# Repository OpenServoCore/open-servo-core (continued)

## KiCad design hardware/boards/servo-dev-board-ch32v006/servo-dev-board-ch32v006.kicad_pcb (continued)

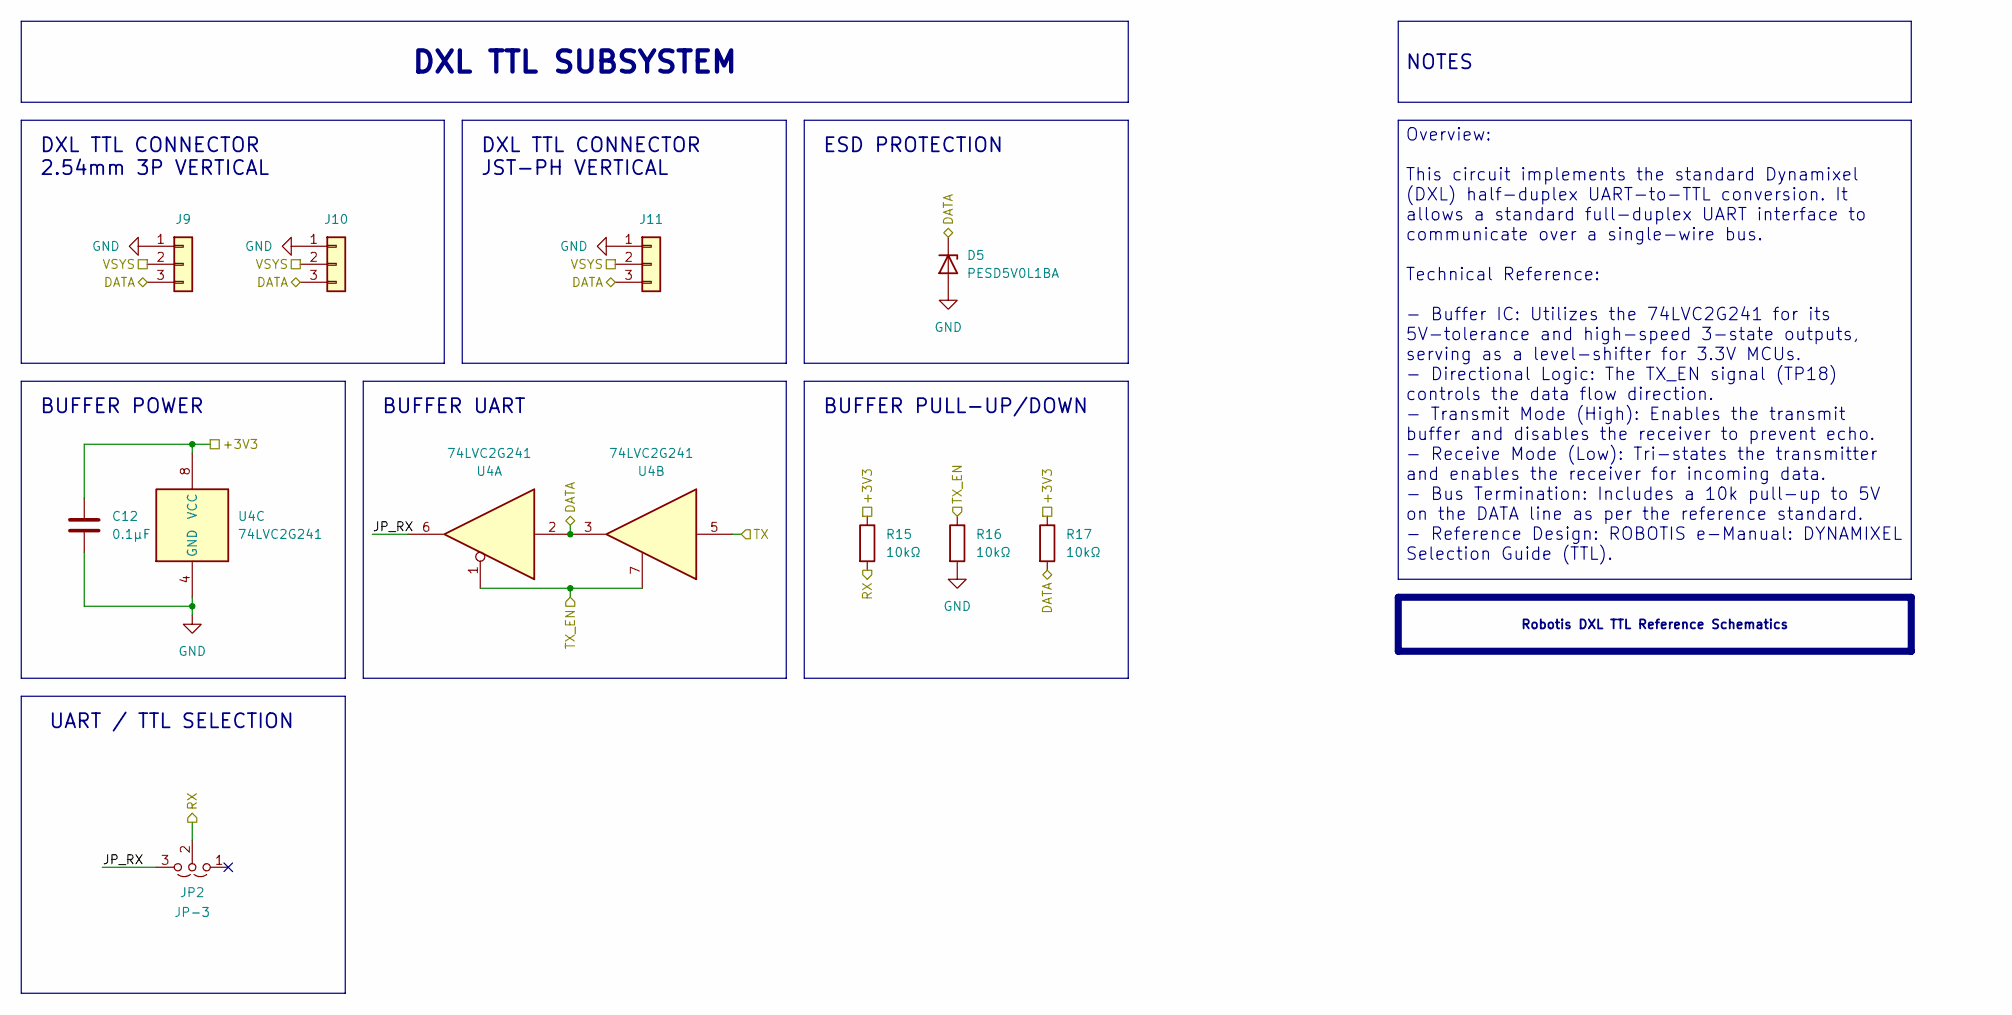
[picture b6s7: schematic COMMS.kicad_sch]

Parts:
C12: 0.1µF; C_0805_2012Metric_Pad1.18x1.45mm_HandSolder; LCSC C28233
D5: PESD5V0L1BA; D_SOD-323_HandSoldering; LCSC C2687118
J9, J10: PIN-1-3P; PinHeader_1x03_P2.54mm_Vertical; LCSC C49257
J11: JST-PH-V; CONN-TH_B3B-PH-K-S; JLC Type Extended
JP2: JP-3; PinHeader_1x03_P2.54mm_Vertical; LCSC C41425293
R15, R16, R17: 10kΩ; R_0805_2012Metric_Pad1.20x1.40mm_HandSolder; LCSC C17414
U4: 74LVC2G241; VSSOP-8_L2.3-W2.0-P0.50-LS3.1-BR; LCSC C10430

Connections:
+3V3: C12.1, R15.1, R17.1, U4.8 (VCC); also elsewhere on the board
/COMMS/JP_RX: JP2.3 (B), U4.6
/DATA: D5.1 (K), J9.3, J10.3, J11.3, R17.2, U4.2, U4.3; also elsewhere on the board
/RX: JP2.2 (C), R15.2; also elsewhere on the board
/TX: U4.5; also elsewhere on the board
/TX_EN: R16.1, U4.1, U4.7; also elsewhere on the board
GND: C12.2, D5.2 (A), J9.1, J10.1, J11.1, R16.2, U4.4 (GND); also elsewhere on the board
VSYS: J9.2, J10.2, J11.2; also elsewhere on the board

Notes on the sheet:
ESD PROTECTION
BUFFER UART
BUFFER PULL-UP/DOWN
DXL TTL CONNECTOR JST-PH VERTICAL
BUFFER POWER
UART / TTL SELECTION
DXL TTL CONNECTOR 2.54mm 3P VERTICAL
Overview: This circuit implements the standard Dynamixel (DXL) half-duplex UART-to-TTL conversion. It allows a standard full-duplex UART interface to communicate over a single-wire bus. Technical Reference: - Buffer IC: Utilizes the 74LVC2G241 for its 5V-tolerance and high-speed 3-state outputs, se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
DXL TTL SUBSYSTEM
Robotis DXL TTL Reference Schematics
NOTES

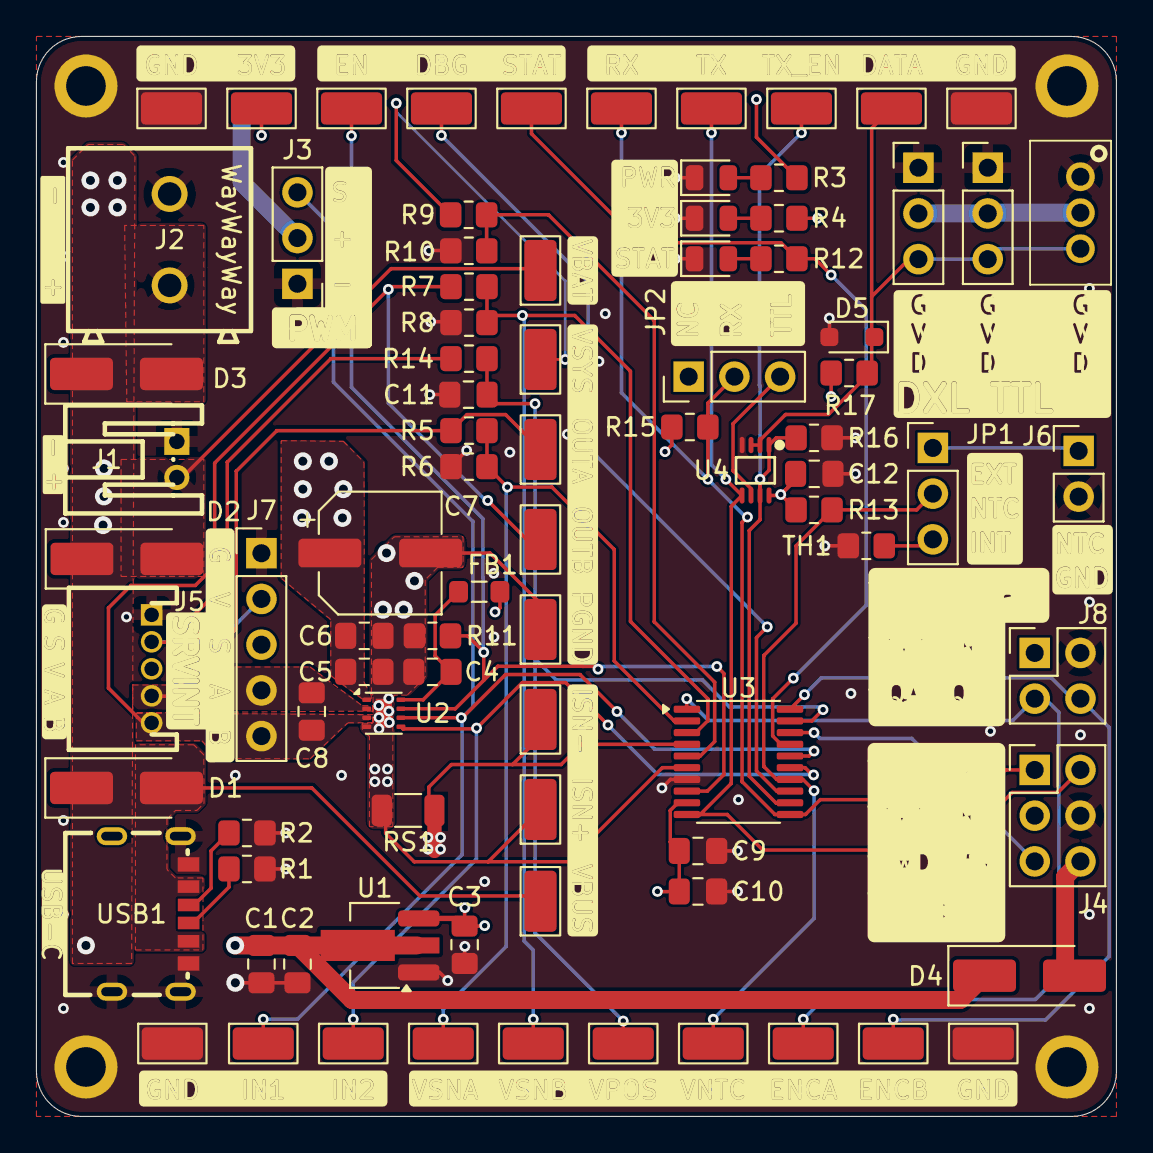
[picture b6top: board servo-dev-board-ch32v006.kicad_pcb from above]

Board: 4 copper layers, 60.0 x 60.0 mm, 92 parts (0 on the bottom side), 39 nets.

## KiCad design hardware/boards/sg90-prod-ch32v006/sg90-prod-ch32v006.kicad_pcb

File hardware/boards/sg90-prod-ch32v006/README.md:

# OSC SG90 CH32

> ⚠️ **Designed, not spun. Pre-fabrication, pre-bringup.**
> This board has never been fabbed. Numbers and behaviour described below are **design intent**, not measured. The schematic and layout exist; the firmware they're meant to run does not yet — firmware v2 is unstarted as of this writing. Don't fab this without doing your own review first, and expect changes when bringup finally happens.

OpenServoCore swap board for SG90-class hobby servos. Compact, double-sided, designed to physically replace the factory PCB inside an SG90 case. CH32V006-based, DXL-compatible half-duplex UART, drop-in mechanical fit.

## Overview

- **MCU** — CH32V006F8U6 (RISC-V, 48 MHz, 62 KB flash, 8 KB RAM).
- **Motor driver** — TI DRV8837 H-bridge (1.8 A peak, IN1/IN2 PWM).
- **LDO** — TPAP2210K-3.3, 3.3 V logic rail.
- **UART buffer** — SN74LVC1G07 open-drain for half-duplex DXL.
- **Current shunt** — 25 mΩ, 1 % on the low side.
- **Power input** — 3.3-8.4 V (1S-2S LiPo) via the servo cable.
- **Debug** — 4-pad SWD interface for WCH-LinkE.
- **Position feedback** — existing servo potentiometer wiper.
- **Form factor** — 10 × 12.5 mm, double-sided assembly.

## Connectors

### Servo cable — J1 (1×3, through-hole pads)

Standard hobby-servo 3-wire pinout, but the signal pin carries half-duplex UART instead of PWM:

| Pin | Net    | Notes                                   |
| --- | ------ | --------------------------------------- |
| 1   | `VIN`  | 3.3-8.4 V (1S-2S LiPo).                 |
| 2   | `DATA` | Half-duplex UART, baud TBD by firmware. |
| 3   | `GND`  |                                         |

### Motor — J2 (2 wire pads)

Solder directly to the SG90 motor leads.

| Pad    | Net              |
| ------ | ---------------- |
| `OUTA` | Motor terminal A |
| `OUTB` | Motor terminal B |

### Potentiometer — J3 (3 pads)

Connects to the existing servo potentiometer.

| Pad    | Net          |
| ------ | ------------ |
| `+3V3` | Pot top rail |
| `VPOS` | Wiper        |
| `GND`  | Pot ground   |

### Debug — J4 (4 pads, 1.27 mm pitch)

Single-wire SWD for WCH-LinkE. Programmed via `wlink` / `probe-rs`. Firmware build instructions land when firmware v2 starts; until then there's nothing to flash.

| Pad | Net     |
| --- | ------- |
| 1   | `+3V3`  |
| 2   | `GND`   |
| 3   | `SWDIO` |
| 4   | `NC`    |

## Design intent

These are the targets the board was laid out around. None are measured.

- **Power architecture** — VIN routes to the DRV8837 directly; 3.3 V logic rail off the TPAP2210K LDO. Bulk capacitance is 2× 10 µF on VIN. PGND/GND joined at a single net tie.
- **Position sensing** — 12-bit ADC on `VPOS` with an RC filter (10 kΩ + 100 nF, fc ≈ 160 Hz) to suppress wiper noise. Sub-degree resolution is the design goal; actual precision waits on bringup and firmware oversampling.
- **Voltage sensing** — 20 kΩ / 10 kΩ dividers (ratio 0.333) on `VINS`, `VSNA`, `VSNB`. 8.4 V → 2.8 V at the ADC.
- **Current sensing** — 25 mΩ low-side shunt, sized for the DRV8837's ~1.76 A peak via `R_shunt ≈ 44 mV / I_stall`, so the hardware stall-detect path trips near the driver's max output. Raw V_shunt = 25 mV at 1 A; firmware sets ADC sampling, gain path, and software overcurrent threshold.
- **Communication** — DXL-style half-duplex UART. The SN74LVC1G07 open-drain buffer enables bidirectional comms over the single `DATA` line. Baud rate TBD — left to firmware v2 to choose.
- **Protection** — PESD5V0L1UL TVS on `DATA`.

## Assembly

Double-sided assembly, no vias-in-pads. Suitable for hot-plate / hot-air / IR reflow, or JLCPCB SMT. The board is 8-layer for routing density at this size.

## Mechanical fit

Designed to drop into a standard SG90 servo case:

- Motor leads solder to `OUTA` / `OUTB`.
- Pot wiper connects to `J3`.
- Servo cable connects to `J1`.
- Debug pads remain accessible through the case opening for bringup / reflashing.

Pad spacing for motor leads and debug pitch are still **to be confirmed against a physical case** when first boards arrive.

## License

Hardware files (schematic, layout, board files in this directory) are licensed under [CERN-OHL-P v2.0](../../../LICENSE-HARDWARE). See the [top-level README](../../../README.md#license) for the full licensing picture.

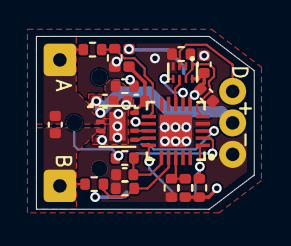
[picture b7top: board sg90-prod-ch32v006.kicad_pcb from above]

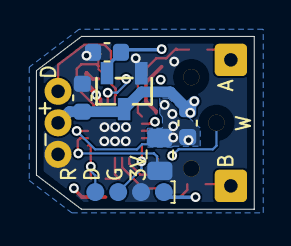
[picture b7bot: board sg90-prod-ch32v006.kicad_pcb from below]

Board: 4 copper layers, 12.1 x 9.6 mm, 31 parts (8 on the bottom side), 23 nets.

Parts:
C1, C2, C10: 10µF; C_0603_1608Metric
C4, C6, C7, C8, C9, C11: 0.1µF; C_0402_1005Metric
FB1: 600Ω@100MHz; L_0402_1005Metric
J1: Servo Input; Servo_Output_Pads
J2: Motor; Motor_Wire_Pads
J3: Debug; Debug_Pads_1x4_P1.27mm
J4: Potentiometer; Pot_Wire_Pads
NT1, NT2: NetTie_2; NetTie-2_SMD_0.127mm
R1, R3, R4, R6, R8, R9: 10kΩ; R_0402_1005Metric
R2: 4.7kΩ; R_0402_1005Metric
R5, R7: 20kΩ; R_0402_1005Metric
RS1: 10mΩ 1%; R_0805_2012Metric
TH1: NTC 10k; R_0402_1005Metric
U1: H7133-1_C277537; SOT-23-3_L2.9-W1.3-P1.90-LS2.4-BR
U4: DRV8837; WSON-8-1EP_2x2mm_P0.5mm_EP0.9x1.6mm
U5: CH32V006F8U6; UQFN-20_L3.0-W3.0-P0.40-BL-EP1.7
U6: 74LVC2G241GS,115; XSON-8_L1.4-W1.0-P0.35-S0.55-BL

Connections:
+3V3: C2.1, C4.1, C11.1, FB1.1, J3.1, J4.3, R4.1, R9.1, U1.2 (VOUT), U5.6 (VDD), U6.8 (VCC)
/3V3_DRV: C7.1, FB1.2, U4.8 (VCC)
/DATA: J1.3, U6.2 (1A), U6.3 (2Y)
/EN: R3.1, U4.7 (~SLEEP), U5.12 (PC5/T1C2_7)
/IN1: U4.6 (IN1), U5.13 (PC6/T1C1_2)
/IN2: U4.5 (IN2), U5.14 (PC7/T1C3_3)
/ISNS+: NT1.1, U5.3 (PA2/OPP0)
/ISNS-: NT2.1, U5.2 (PA1/OPN0)
/MOT_A: C8.1, J2.1, R5.1, U4.2 (OUT1)
/MOT_B: C8.2, J2.2, R7.1, U4.3 (OUT2)
/POT: J4.2, R2.1
/RX: U5.8 (PC1/RX_3), U6.6 (1Y)
/SWDIO: J3.3, U5.15 (PD1/SWIO)
/TX: U5.7 (PC0/TX_3/T1C3_2), U6.5 (2A)
/TX_EN: R1.2, U5.5 (PD0/TX_2), U6.1 (~1OE), U6.7 (2OE)
/VNTC: R9.2, TH1.1, U5.18 (PD4/A7)
/VPOS: C6.1, R2.2, U5.16 (PD2/A3)
/VSNA: R5.2, R6.1, U5.11 (PC4/A2)
/VSNB: R7.2, R8.1, U5.17 (PD3/A4)
/nRST: J3.4, R4.2, U5.1 (PD7/RST)
GND: C1.2, C2.2, C4.2, C6.2, C11.2, J1.1, J3.2, J4.1, NT2.2, R1.1, R6.2, R8.2, RS1.1, TH1.2, U1.1 (GND), U5.4 (VSS), U5.21 (VSS), U6.4 (GND)
PGND: C7.2, C9.2, C10.2, NT1.2, R3.2, RS1.2, U4.4 (GND), U4.9 (GND)
VSYS: C1.1, C9.1, C10.1, J1.2, U1.3 (VIN), U4.1 (VM)

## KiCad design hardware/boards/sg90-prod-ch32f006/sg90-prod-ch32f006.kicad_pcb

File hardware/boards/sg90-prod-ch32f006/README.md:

# SG90 Servo Controller Board - CH32V006

A compact, high-precision servo controller designed to replace the control circuitry in SG90/MG90 servo clones. This single-sided board fits within a 10x12.5mm footprint while providing advanced features like back-EMF sensing, overcurrent protection, and 0.1-0.2° position precision.

## Features

- **MCU**: CH32V006F8U6 RISC-V microcontroller (48MHz, 32KB flash, 4KB RAM)
- **Motor Driver**: Integrated DRV8837C H-bridge (1.8A peak)
- **Position Sensing**: 12-bit ADC with RC filtering for 0.1-0.2° precision
- **Current Sensing**: 0.1Ω shunt with internal op-amp
- **Protection**: P-channel MOSFET reverse polarity protection (17mΩ RDS(on))
- **Communication**: 2Mbps half-duplex UART over single DATA line
- **Power**: 5V operation, no LDO required
- **Size**: 10x12.5mm, single-sided assembly
- **Debug**: 4-pin SWD interface for programming with WCH-LinkE

## Specifications

- Input Voltage: 4.5-5.5V
- Continuous Current: 200mA (typical servo operation)
- Peak Current: 1A (stall condition)
- Position Resolution: 0.044°/count (4096 counts over 180°)
- PWM Frequency: 10kHz center-aligned
- Communication: 2Mbps half-duplex UART
- Temperature Range: -40°C to +85°C

## Bill of Materials (BOM)

| Ref | Description | Package | LCSC # | Qty | Unit Price @5 | Unit Price @150 | Unit Price @500 |
|-----|-------------|---------|--------|-----|---------------|-----------------|-----------------|
| U1 | CH32V006F8U6 MCU | QFN-20 3x3mm | C42431288 | 1 | $0.2643 | $0.1838 | $0.1537 |
| U2 | DRV8837CDSGR Motor Driver | WSON-8 | C191000 | 1 | $0.098 | $0.0666 | $0.0587 |
| U3 | 74LVC1G07DSFR Buffer | TDFN-6 1x1mm | C42445855 | 1 | $0.0466 | $0.0317 | $0.0280 |
| Q1 | BRCS150P02ZJ P-MOSFET | DFN-6 2x2mm | C22448985 | 1 | $0.0747 | $0.0522 | $0.0466 |
| R1 | 10kΩ 1% | 0603 | Generic | 1 | $0.01 | $0.002 | $0.002 |
| R2 | 0.1Ω 1% 1/4W | 0603/0805 | Generic | 1 | $0.02 | $0.003 | $0.003 |
| R3 | 10kΩ 1% | 0603 | Generic | 1 | $0.01 | $0.002 | $0.002 |
| R4,R5 | 10kΩ 1% | 0603 | Generic | 2 | $0.01 | $0.002 | $0.002 |
| R6,R7 | 0Ω | 0603 | Generic | 2 | $0.01 | $0.001 | $0.001 |
| R8 | 0Ω | 0603 | Generic | 1 | $0.01 | $0.001 | $0.001 |
| R9 | 10kΩ 1% | 0603 | Generic | 1 | $0.01 | $0.002 | $0.002 |
| R10 | 1kΩ 1% | 0603 | Generic | 1 | $0.01 | $0.002 | $0.002 |
| C1,C2 | 100nF 16V X7R | 0603 | Generic | 2 | $0.01 | $0.002 | $0.002 |
| C3 | 1µF 16V X7R | 0603 | Generic | 1 | $0.01 | $0.003 | $0.003 |
| C4,C5 | 10µF 10V X5R | 0603/0805 | Generic | 2 | $0.02 | $0.005 | $0.004 |
| C6 | 100nF 16V X7R | 0603 | Generic | 1 | $0.01 | $0.002 | $0.002 |
| **Components Total** | | | | | **$0.664** | **~$0.35** | **$0.326** |
| **PCB** | 10x12.5mm 4-layer | - | - | 1 | **$1.40** | **$0.25** | **$0.11** |
| **TOTAL per board** | | | | | **$2.064** | **$0.60** | **$0.436** |
| **TOTAL** | | | | | **$10.32** | **$90.00** | **$218.00** |

### Cost Breakdown by Quantity

#### Prototype Run (5 boards)
- Components (5 sets): $0.664 × 5 = $3.32
- PCB (5 boards): $2.00 + $5.00 shipping = $7.00
- **Total for 5 boards: $10.32**
- **Cost per board: $2.06**
- **Selling at $3/board: $15 revenue - Profit: $4.68 (45% margin)**
- **Selling at $5/board: $25 revenue - Profit: $14.68 (142% margin)**

#### Small Production (150 boards)
- Components (150 sets): ~$0.35 × 150 = $52.50
- PCB (150 boards): $32.00 + $5.00 shipping = $37.00
- **Total for 150 boards: $89.50**
- **Cost per board: $0.60**
- **Selling at $2-3/board: $300-450 revenue**
- **Gross profit: $210.50-360.50**

#### Medium Production (500 boards)
- Components (500 sets): $0.326 × 500 = $163.00
- PCB (500 boards): $50.20 + $5.00 shipping = $55.20
- **Total for 500 boards: $218.20**
- **Cost per board: $0.44**
- **Selling at $2/board: $1,000 revenue**
- **Gross profit: $781.80 (358% markup!)**

*Prices shown are from LCSC in USD. Passive component prices are estimates for generic parts.*

## Pinout

### Power Connector (J1) - 3 pins
1. V_IN (5V)
2. DATA (Half-duplex UART, 2Mbps)
3. GND

### Motor Connector (J3) - 2 wire pads
1. MOT_A - Motor terminal A (7.4mm spacing)
2. MOT_B - Motor terminal B

### Potentiometer Connector (J2) - 3 pads
1. POT_VCC - Potentiometer power (5V)
2. POT_WIPER - Position feedback
3. POT_GND - Potentiometer ground

### Debug Interface (J4) - 4 pads, 1.27mm pitch
1. 5V - Power from debugger
2. GND - Ground
3. SWDIO - Single-wire debug
4. NC - Not connected

## Design Notes

### Power Architecture
- Single 5V rail operation eliminates need for LDO
- P-channel MOSFET provides reverse polarity protection with only 17mV drop at 1A
- Bulk capacitance (2x10µF) handles motor transients
- No ferrite bead needed due to synchronized ADC sampling

### ADC Precision
- 12-bit ADC provides 22.8 counts per degree (0.044°/count theoretical)
- RC filter (1kΩ + 100nF) on POT input reduces wiper noise
- 4-16x oversampling in firmware improves effective resolution
- Center-aligned PWM with mid-duty ADC sampling avoids switching noise

### Current Sensing
- 0.1Ω shunt resistor in series with motor ground
- Internal op-amp amplifies voltage drop
- ADC watchdog enables hardware overcurrent protection
- Kelvin connections (0Ω resistors R6,R7) for accurate sensing

### Communication
- Half-duplex UART at 2Mbps over single DATA line
- 74LVC1G07 open-drain buffer enables bidirectional communication
- 10kΩ pullup (R1) sized for 2Mbps operation
- Compatible with standard servo protocols

## Assembly

This board is designed for single-sided assembly, making it ideal for:
- Hot plate reflow
- Hot air station
- IR oven
- JLCPCB assembly service

All components are on the top side with no vias in pads.

## Programming

Program using WCH-LinkE debugger/programmer:
- Supports 5V target voltage
- Single-wire debug (SWD) interface
- Compatible with MounRiver Studio IDE
- printf debugging available over SWD

## Mechanical Integration

The board is designed to fit inside standard SG90 servo cases:
- Motor wires solder directly to MOT_A/MOT_B pads
- Potentiometer wires connect to J2
- Servo cable connects to J1
- Debug pads accessible through case opening

## Performance Targets

- Position accuracy: ±0.1-0.2°
- Position resolution: 0.044°
- Update rate: 10kHz
- Current limit: 1A (configurable via firmware)
- Continuous operation: 200mA
- Response time: <1ms
- Backdrive detection: Yes (via back-EMF)

## Manufacturing

Optimized for low-cost production:
- Total BOM cost: ~$0.43 at 500 qty
- Single-sided assembly reduces assembly cost
- Standard 0603 passives (except current shunt)
- All components available from LCSC
- 4-layer PCB for better thermal management

## TODO / Future Improvements

### Critical Values to Double-Check Before PCB Routing
- [ ] **Current shunt (R2):** Verify 0.1Ω gives good ADC range (0-330mV at 1A through 3.3x op-amp gain)
- [ ] **Voltage dividers (R4/R5):** Confirm 10kΩ divider properly scales 5V motor to ADC range
- [ ] **UART pullup (R1):** Verify 10kΩ optimal for 2Mbps half-duplex
- [ ] **RC filter (R10/C6):** Check 1kΩ + 100nF = 1.6kHz cutoff for POT noise
- [ ] **Bulk caps (C4/C5):** Confirm 2x10µF sufficient for motor transients
- [ ] **P-MOSFET RDS(on):** Verify 17mΩ = 17mV drop at 1A peak is acceptable
- [ ] **Motor pad spacing:** Confirm 7.4mm (3.7mm each side from center)
- [ ] **Debug pad pitch:** Verify 1.27mm for pogo pins
- [ ] **Package sizes:** Verify all footprints match actual parts (especially QFN-20)

### Rev B Changes
1. **Add test points on back side**
   - Add second 1x4 array at 1.27mm pitch (same as debug interface)
   - Uses same pogo pin clip for both programming and testing
   - **Debug array (1x4):** 5V, GND, SWDIO, NC (existing)
   - **Test array (1x4):** SEN_I, SEN_POT, PWM_A, V_MCU
   - Both arrays accessible from back when installed in servo
   - *Rationale: Single pogo clip tool works for both debug and test*

2. **Add ESD protection**
   - TVS diode on DATA line (SOD-523 or 0402 package)
   - Protects against ESD during cable plug/unplug
   - Suggested part: PESD5V0S1BL or similar 5.5V TVS (~$0.05)

3. **Consider fiducial marker**
   - Single 1mm fiducial for JLCPCB assembly alignment
   - Only if assembly house requires it

### Firmware Features (Planned)
- Backlash compensation
- Temperature compensation
- Position calibration LUT
- Multi-drop addressing
- Synchronized motion commands

## License

[Add your license here]

## Author

[Add author information here]

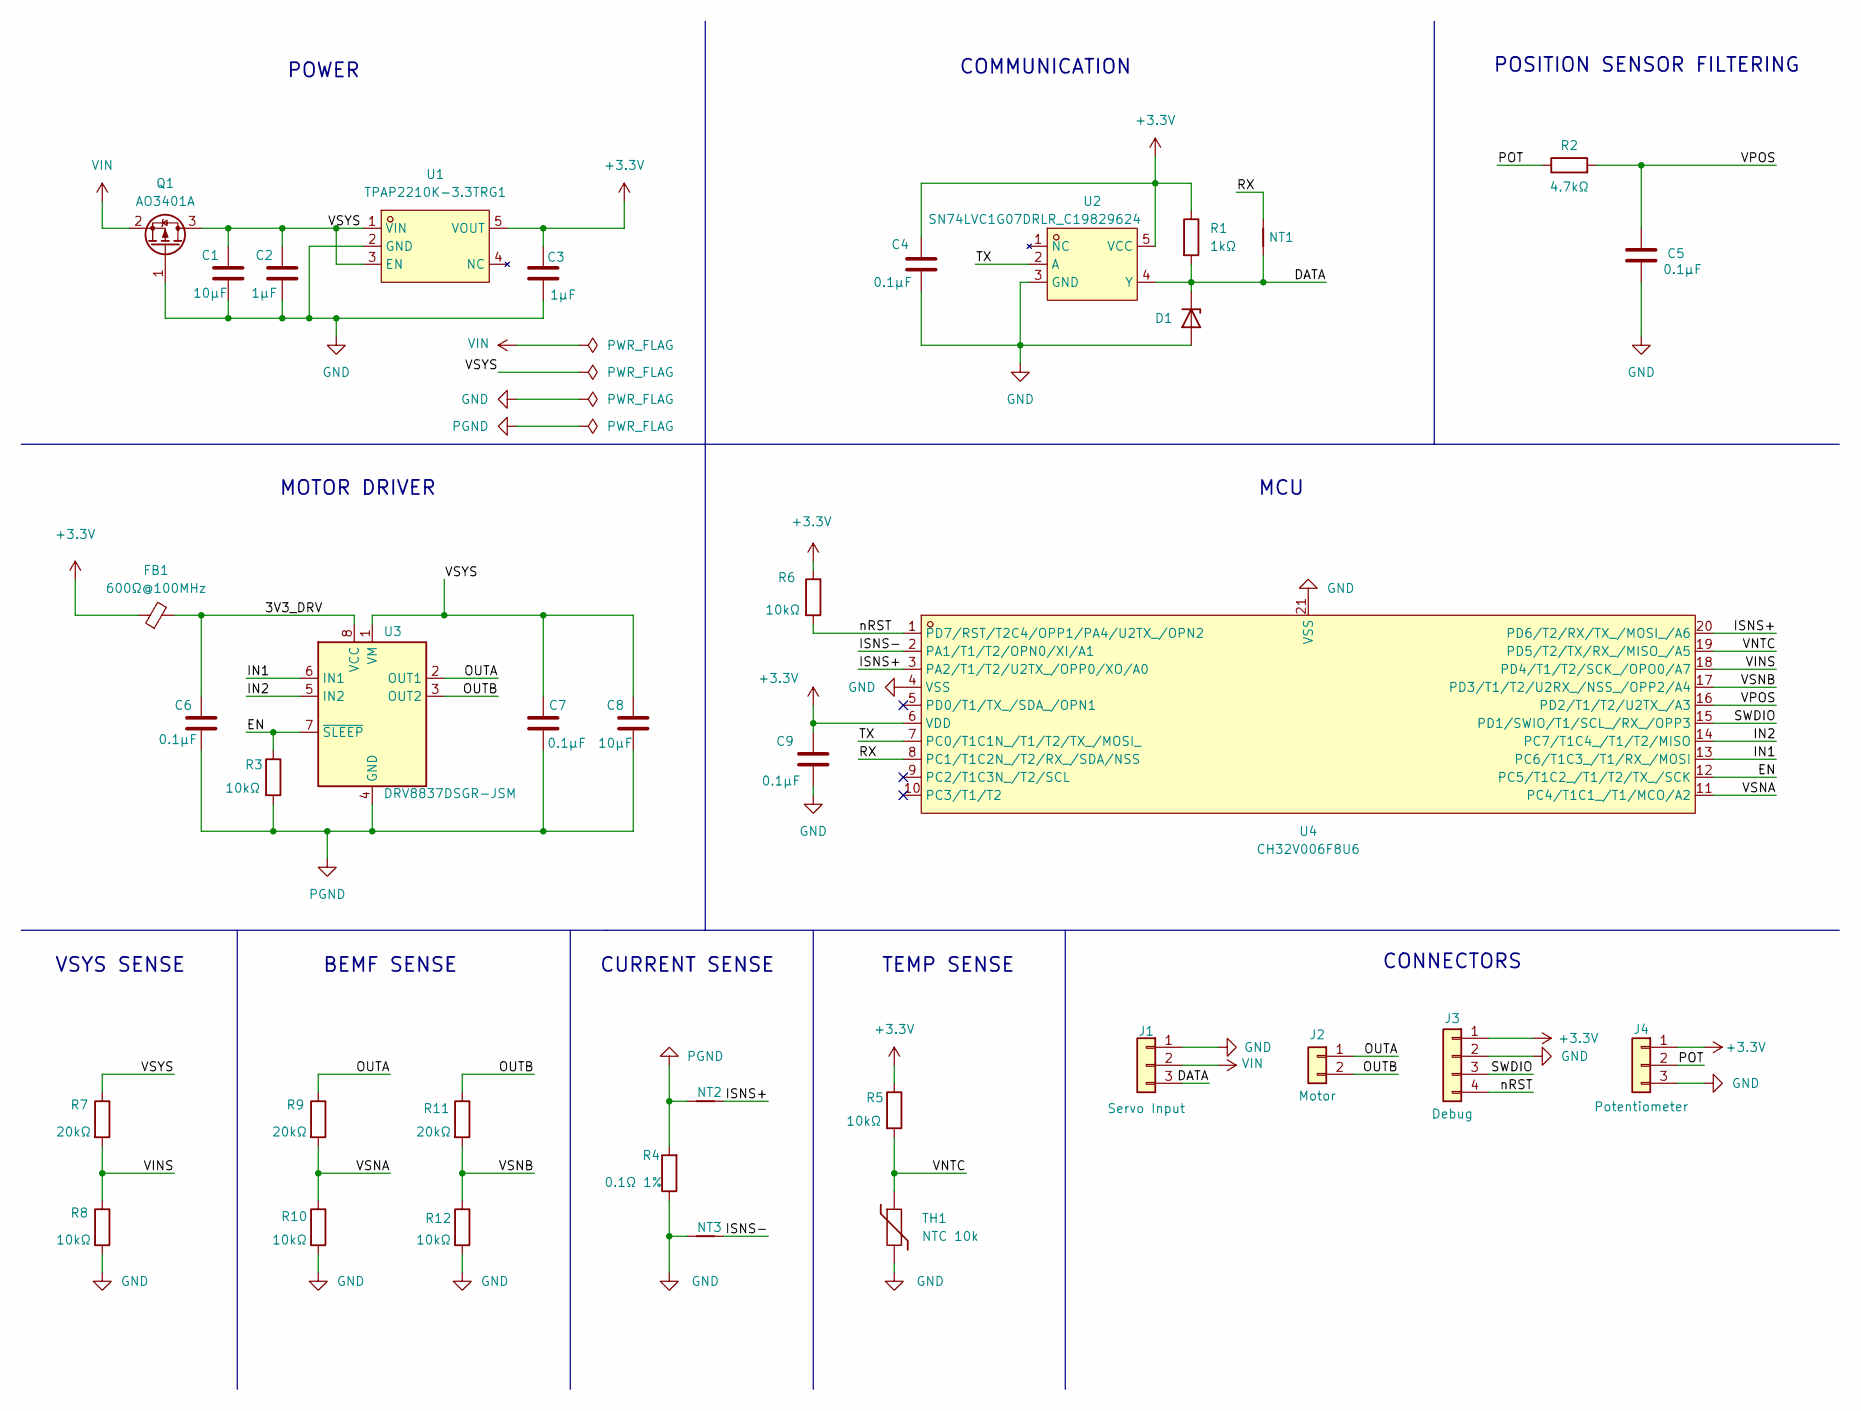
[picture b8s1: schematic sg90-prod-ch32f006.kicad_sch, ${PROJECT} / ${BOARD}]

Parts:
C1, C8: 10µF; C_0603_1608Metric
C2, C3: 1µF; C_0402_1005Metric
C4, C5, C6, C7, C9: 0.1µF; C_0402_1005Metric
D1: PESD5V0L1UL; D_SOD-882
FB1: 600Ω@100MHz; L_0603_1608Metric
J1: Servo Input; Servo_Output_Pads
J2: Motor; Motor_Wire_Pads
J3: Debug; Debug_Pads_1x4_P1.27mm
J4: Potentiometer; Pot_Wire_Pads
NT1, NT2, NT3: NetTie_2; NetTie-2_SMD_0.2mm
Q1: AO3401A; SOT-23
R1: 1kΩ; R_0402_1005Metric
R2: 4.7kΩ; R_0402_1005Metric
R3, R5, R6, R8, R10, R12: 10kΩ; R_0402_1005Metric
R4: 0.1Ω 1%; R_1206_3216Metric
R7, R9, R11: 20kΩ; R_0402_1005Metric
TH1: NTC 10k; R_0402_1005Metric
U1: TPAP2210K-3.3TRG1; SOT-23-5_L2.9-W1.6-P0.95-LS2.8-BR; LCSC Part C49190789
U2: SN74LVC1G07DRLR_C19829624; SOT-553-5_L1.6-W1.2-P0.50-LS1.6-BL; LCSC Part C19829624
U3: DRV8837DSGR-JSM; WSON-8-1EP_2x2mm_P0.5mm_EP0.9x1.6mm; LCSC C22447132
U4: CH32V006F8U6; UQFN-20_L3.0-W3.0-P0.40-BL-EP1.7; LCSC Part C42431288

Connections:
+3.3V: C3.1, C4.1, C9.1, FB1.1, J3.1, J4.1, R1.1, R5.1, R6.1, U1.5 (VOUT), U2.5 (VCC), U4.6 (VDD)
/3V3_DRV: C6.1, FB1.2, U3.8 (VCC)
/DATA: D1.1 (K), J1.3, NT1.2, R1.2, U2.4 (Y)
/EN: R3.1, U3.7 (~SLEEP), U4.12 (PC5/T1C2_/T1/T2/TX_/SCK)
/IN1: U3.6 (IN1), U4.13 (PC6/T1C3_/T1/RX_/MOSI)
/IN2: U3.5 (IN2), U4.14 (PC7/T1C4_/T1/T2/MISO)
/ISNS+: NT2.1, U4.3 (PA2/T1/T2/U2TX_/OPP0/XO/A0), U4.20 (PD6/T2/RX/TX_/MOSI_/A6)
/ISNS-: NT3.1, U4.2 (PA1/T1/T2/OPN0/XI/A1)
/OUTA: J2.1, R9.1, U3.2 (OUT1)
/OUTB: J2.2, R11.1, U3.3 (OUT2)
/POT: J4.2, R2.1
/RX: NT1.1, U4.8 (PC1/T1C2N_/T2/RX_/SDA/NSS)
/SWDIO: J3.3, U4.15 (PD1/SWIO/T1/SCL_/RX_/OPP3)
/TX: U2.2 (A), U4.7 (PC0/T1C1N_/T1/T2/TX_/MOSI_)
/VINS: R7.2, R8.1, U4.18 (PD4/T1/T2/SCK_/OPO0/A7)
/VNTC: R5.2, TH1.1, U4.19 (PD5/T2/TX/RX_/MISO_/A5)
/VPOS: C5.1, R2.2, U4.16 (PD2/T1/T2/U2TX_/A3)
/VSNA: R9.2, R10.1, U4.11 (PC4/T1C1_/T1/MCO/A2)
/VSNB: R11.2, R12.1, U4.17 (PD3/T1/T2/U2RX_/NSS_/OPP2/A4)
/VSYS: C1.1, C2.1, C7.1, C8.1, Q1.3 (D), R7.1, U1.1 (VIN), U1.3 (EN), U3.1 (VM)
/nRST: J3.4, R6.2, U4.1 (PD7/RST/T2C4/OPP1/PA4/U2TX_/OPN2)
GND: C1.2, C2.2, C3.2, C4.2, C5.2, C9.2, D1.2 (A), J1.1, J3.2, J4.3, NT3.2, Q1.1 (G), R4.1, R8.2, R10.2, R12.2, TH1.2, U1.2 (GND), U2.3 (GND), U4.4 (VSS), U4.21 (VSS)
PGND: C6.2, C7.2, C8.2, NT2.2, R3.2, R4.2, U3.4 (GND), U3.9 (GND)
VIN: J1.2, Q1.2 (S)

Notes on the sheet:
VSYS SENSE
POWER
MOTOR DRIVER
BEMF SENSE
CONNECTORS
TEMP SENSE
CURRENT SENSE
COMMUNICATION
MCU
POSITION SENSOR FILTERING

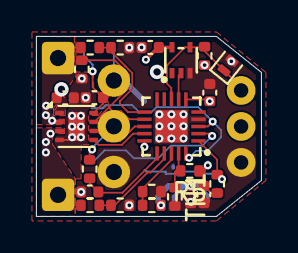
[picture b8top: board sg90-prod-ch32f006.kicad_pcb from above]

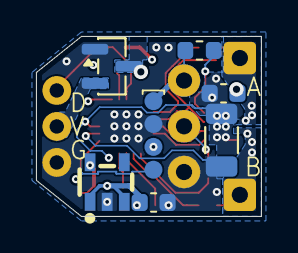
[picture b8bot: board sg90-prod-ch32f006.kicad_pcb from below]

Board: 6 copper layers, 12.5 x 10.0 mm, 36 parts (11 on the bottom side), 24 nets.

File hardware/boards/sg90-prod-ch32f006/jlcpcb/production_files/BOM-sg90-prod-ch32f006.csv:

Comment,Designator,Footprint,LCSC,Quantity
0.1µF,"C4,C5,C6,C7,C9",C_0402_1005Metric,C1525,5
0.1Ω 1%,R4,R_1206_3216Metric,C25334,1
10kΩ,"R10,R12,R3,R5,R6,R8",R_0402_1005Metric,C25744,6
10µF,"C1,C8",C_0603_1608Metric,C96446,2
1kΩ,R1,R_0402_1005Metric,C11702,1
1µF,"C2,C3",C_0402_1005Metric,C52923,2
20kΩ,"R11,R7,R9",R_0402_1005Metric,C25764,3
4.7kΩ,R2,R_0402_1005Metric,C25900,1
600Ω@100MHz,FB1,L_0603_1608Metric,C1002,1
AO3401A,Q1,SOT-23,C15127,1
CH32V006F8U6,U4,UQFN-20_L3.0-W3.0-P0.40-BL-EP1.7,C42431288,1
DRV8837DSGR-JSM,U3,WSON-8-1EP_2x2mm_P0.5mm_EP0.9x1.6mm,C22447132,1
NTC 10k,TH1,R_0402_1005Metric,C77131,1
PESD5V0L1UL,D1,D_SOD-882,C3001948,1
SN74LVC1G07DRLR_C19829624,U2,SOT-553-5_L1.6-W1.2-P0.50-LS1.6-BL,C19829624,1
TPAP2210K-3.3TRG1,U1,SOT-23-5_L2.9-W1.6-P0.95-LS2.8-BR,C49190789,1

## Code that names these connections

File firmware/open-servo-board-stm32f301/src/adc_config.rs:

//! Feature-gated ADC channel configuration.
//!
//! The ADC sequence length depends on enabled features:
//! - Always: VREFINT, position (ch1)
//! - current-sense-bus: current sense (ch2)
//! - voltage-sense-motor: voltage dividers (ch3, ch4)
//! - temp-sense-mcu: internal temp sensor (ch16)
//! - temp-sense-motor: NTC thermistor (ch5)

use open_servo_macros::AdcChannels;

#[derive(AdcChannels)]
#[adc_channels(buffer = "AdcBuffer", count = "ADC_CHANNEL_COUNT")]
pub struct Channels<'a> {
    buf: &'a [u16],

    /// VREFINT (internal voltage reference).
    #[channel(name = "VREFINT")]
    _vrefint: (),

    /// Position sensor (PA0, ADC1_IN1).
    #[channel(name = "POSITION")]
    _position: (),

    /// Current sense (PA1, ADC1_IN2).
    #[cfg(feature = "current-sense-bus")]
    #[channel(name = "CURRENT")]
    _current: (),

    /// Motor voltage A (PA2, ADC1_IN3).
    #[cfg(feature = "voltage-sense-motor")]
    #[channel(name = "VOLTAGE_A")]
    _voltage_a: (),

    /// Motor voltage B (PA3, ADC1_IN4).
    #[cfg(feature = "voltage-sense-motor")]
    #[channel(name = "VOLTAGE_B")]
    _voltage_b: (),

    /// Motor temperature NTC (PA4, ADC1_IN5).
    #[cfg(feature = "temp-sense-motor")]
    #[channel(name = "MOTOR_TEMP")]
    _motor_temp: (),

    /// MCU internal temperature sensor (ADC1_IN16).
    #[cfg(feature = "temp-sense-mcu")]
    #[channel(name = "MCU_TEMP")]
    _mcu_temp: (),
}
